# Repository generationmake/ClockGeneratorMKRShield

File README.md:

# ClockGeneratorMKRShield
Shield with Si5351 clock generator and output filter for Arduino MKR

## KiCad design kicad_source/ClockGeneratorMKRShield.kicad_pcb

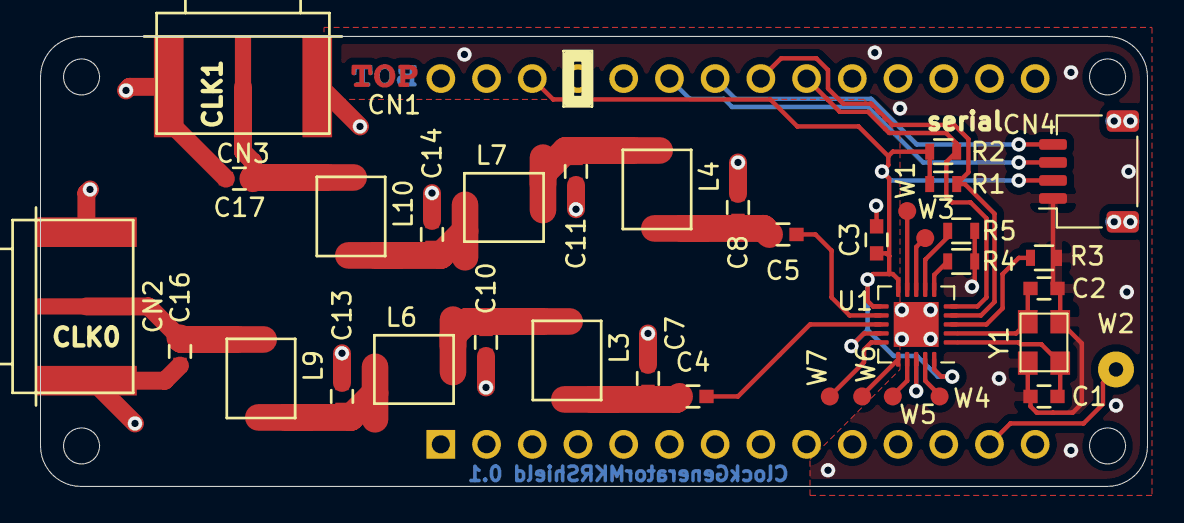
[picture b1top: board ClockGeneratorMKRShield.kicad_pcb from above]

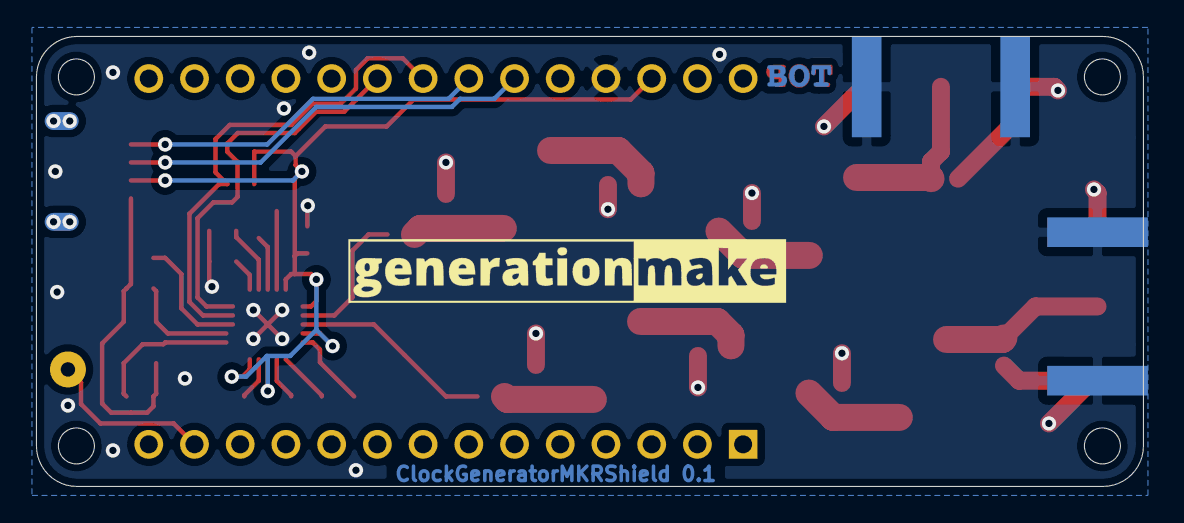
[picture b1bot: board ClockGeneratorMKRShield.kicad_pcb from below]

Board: 2 copper layers, 61.5 x 25.0 mm, 41 parts (2 on the bottom side), 28 nets.

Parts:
C1, C2: DNI; C_0603
C3: 100 nF; C_0603
C4, C5: 10 nF; C_0603
C7, C16: 30 pF; C_0603
C8, C17: 91 pF; C_0603
C10, C13: 47 pF; C_0603
C11, C14: 130 pF; C_0603
CN1: ARDUINO_MKR; ARDUINO_MKR_HOLES_PINHEADER_EDGE
CN2, CN3: CON-SMA-EDGE-S-ND; WR-SMA-PCB
CN4: SM04B-SRSS-TB; JST_SH_SM04B-SRSS-TB_1x04-1MP_P1.00mm_Horizontal
L1: Label; Top
L2: Label; Bot
L3, L4, L6, L7, L9, L10: 744912212; WE-CAIR_4248
L5: Label; generationmake_small_solder
L8: Label; generationmake_logo
R1, R2: 10k; R_0603
R3, R4, R5: 0R; R_0603
U1: SI5351A_B_GM; QFN-20-1EP_4x4mm_P0.5mm_EP2.5x2.5mm
W1, W3, W4, W5, W6, W7: TEST_1P; SolderWirePad_single_1mmSMD
W2: TEST_1P; SolderWirePad_single_0-8mmDrill
Y1: RH100-25.000-6-F-1010-TR; Crystal_SMD_3.2x2.5mm_4Pad

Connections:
+3V3: C3.1, CN1.26, CN4.2, R1.1, R2.1, U1.10, U1.11, U1.14, U1.18, U1.20
/A0: R3.1, U1.3
/CLK0: C4.2, U1.13
/CLK1: C5.2, U1.12
/OEB: R5.1, U1.7
/PPS_INT: CN1.13, W2.1
/SERIAL_RX: CN1.22, CN4.4
/SERIAL_TX: CN1.23, CN4.3
/SSEN: R4.1, U1.6
/XA: C1.1, U1.1, Y1.1
/XB: C2.1, U1.2, Y1.3
GND: C1.2, C2.2, C3.2, C7.1, C8.1, C10.1, C11.1, C13.1, C14.1, C16.1, C17.1, CN1.25, CN2.2, CN2.3, CN2.4, CN2.5, CN3.2, CN3.3, CN3.4, CN3.5, CN4.1, R3.2, R4.2, R5.2, U1.21, Y1.2, Y1.4
I2C_SCL: CN1.21, R1.2, U1.4
I2C_SDA: CN1.20, R2.2, U1.5
unnamed: C4.1, C7.2, L3.1
unnamed: C5.1, C8.2, L4.1
unnamed: C10.2, L3.2, L6.1
unnamed: C11.2, L4.2, L7.1
unnamed: C13.2, L6.2, L9.1
unnamed: C14.2, L7.2, L10.1
unnamed: C16.2, CN2.1, L9.2
unnamed: C17.2, CN3.1, L10.2
unnamed: U1.8, W3.1
unnamed: U1.9, W1.1
unnamed: U1.15, W7.1
unnamed: U1.16, W6.1
unnamed: U1.17, W5.1
unnamed: U1.19, W4.1

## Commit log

2021-02-03 added kicad project from template
2021-02-03 updated schematic
2021-02-04 generated layout
2021-02-14 added values for filter components
2021-02-14 added connector for gps module
2021-02-19 switched to clock generator in QFN package, updated layout
2022-08-26 added rendering
